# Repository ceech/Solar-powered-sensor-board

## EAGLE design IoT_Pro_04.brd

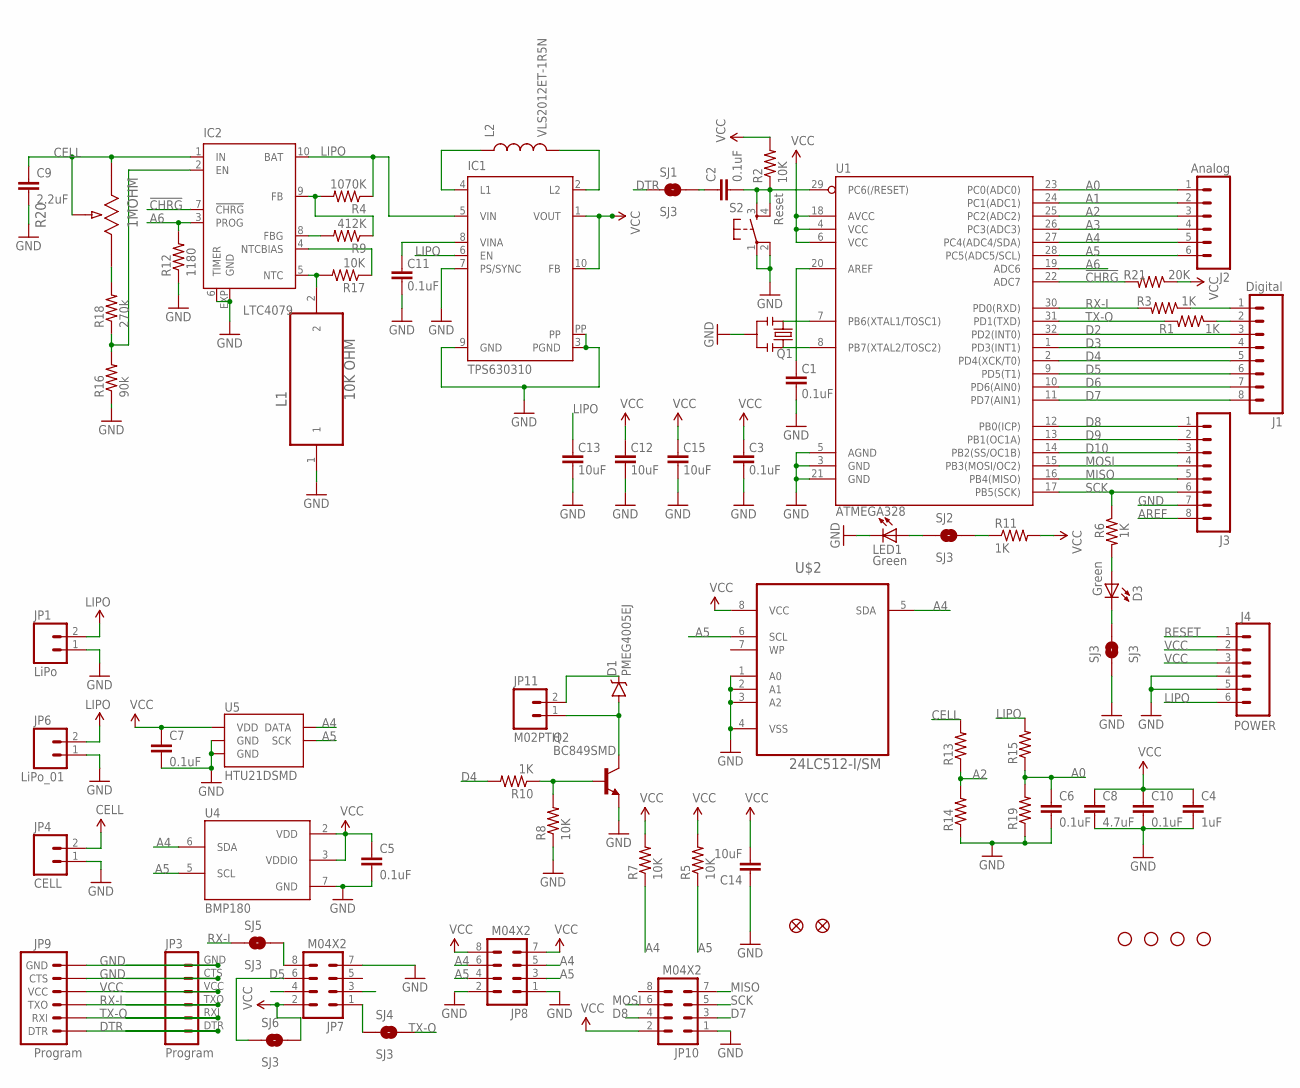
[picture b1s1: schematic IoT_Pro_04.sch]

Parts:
C1, C2, C3, C5, C6, C7, C10, C11: 0.1uF; 0805
C4: 1uF; 0805
C8: 4.7uF; 0805
C9: 2.2uF; 0805
C12, C13, C14, C15: 10uF; 0805
D1: PMEG4005EJ; SOD-323
D3: Green; PLCC2
IC1: TPS630310; S-PDSO-N10
IC2: LTC4079; DFN10-3X3
J1: Digital; 1X08
J2: Analog; 1X06
J3: M081X08; 1X08
J4: POWER; 1X06
JP1: LiPo; MOLEX-1X2
JP2, JP5: FIDUCIAL1X2.5; FIDUCIAL-1X2.5
JP3: Program; 1X06
JP4: CELL; MOLEX-1X2
JP6: LiPo_01; 1X02
JP7, JP8, JP10: M04X2; 2X4
JP9: Program; 1X06-SMD
JP11: M02PTH; 1X02
L1: 10K OHM; THERM_B57421V2103J62
L2: VLS2012ET-1R5N; 1007
LED1: Green; PLCC2
Q1: 8MHZ; RESONATOR-SMD
Q2: BC849SMD; SOT23-BEC
R1, R3, R6, R10, R11: 1K; 0805
R2, R5, R7, R8, R17: 10K; 0805
R4: 1070K; 0805
R9: 412K; 0805
R12: 1180; 0805
R13, R14, R15, R19: RESISTOR0805-RES; 0805
R16: 90k; 0805
R18: 270k; 0805
R20: 1MOHM; POT_EVM2N
R21: 20K; 0805
S2: Reset; TACTILE_SWITCH_SMD
SJ1, SJ2, SJ3, SJ4, SJ5, SJ6: SJ3; SJ_2S-NOTRACE
U1: ATMEGA328; TQFP32-08
U4: BMP180
U5: HTU21DSMD; HTU21D
U$1, U$3, U$9, U$10: STAND-OFFTIGHT; STAND-OFF-TIGHT
U$2: 24LC512-I/SM; SOIC127P794X203-8N

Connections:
!CHRG: IC2.7 (!CHRG), R21.2, U1.22 (ADC7)
A0: C6.1, J2.1, R15.1, R19.2, U1.23 (PC0(ADC0))
A1: J2.2, U1.24 (PC1(ADC1))
A2: J2.3, R13.1, R14.2, U1.25 (PC2(ADC2))
A3: J2.4, U1.26 (PC3(ADC3))
A4: J2.5, JP8.5, JP8.6, R7.1, U1.27 (PC4(ADC4/SDA)), U4.6 (SDA), U5.DATA, U$2.5 (SDA)
A5: J2.6, JP8.3, JP8.4, R5.1, U1.28 (PC5(ADC5/SCL)), U4.5 (SCL), U5.SCK, U$2.6 (SCL)
A6: IC2.3 (PROG), R12.2, U1.19 (ADC6)
AREF: C1.2, J3.8, U1.20 (AREF)
CELL: C9.1, IC2.1 (IN), JP4.2, R13.2, R20.2, R20.3
D2: J1.3, U1.32 (PD2(INT0))
D3: J1.4, U1.1 (PD3(INT1))
D4: J1.5, R10.2, U1.2 (PD4(XCK/T0))
D5: J1.6, JP7.6, SJ6.1, U1.9 (PD5(T1))
D6: J1.7, U1.10 (PD6(AIN0))
D7: J1.8, JP10.3, U1.11 (PD7(AIN1))
D8: J3.1, JP10.4, U1.12 (PB0(ICP))
D9: J3.2, U1.13 (PB1(OC1A))
D10: J3.3, U1.14 (PB2(SS/OC1B))
DTR: JP3.DTR (1), JP9.1 (DTR), SJ1.1
GND: C1.1, C3.1, C4.2, C5.2, C6.2, C7.2, C8.2, C9.2, C10.2, C11.1, C12.1, C13.1, C14.1, C15.1, IC1.3 (PGND), IC1.7 (PS/SYNC), IC1.9 (GND), IC1.PP, IC2.6 (TIMER), IC2.EXP (GND), J3.7, J4.4, J4.5, JP1.1, JP3.CTS (5), JP3.GND (6), JP4.1, JP6.1, JP7.7, JP8.1, JP8.2, JP9.5 (CTS), JP9.6 (GND), JP10.1, L1.1, LED1.C, Q1.2, Q2.E, R8.1, R12.1, R14.1, R16.1, R19.1, S2.1, S2.2, SJ3.1, U1.3 (GND), U1.5 (AGND), U1.21 (GND), U4.7 (GND), U5.7 (GND), U5.GND, U$2.1 (A0), U$2.2 (A1), U$2.3 (A2), U$2.4 (VSS)
LIPO: C13.2, IC1.5 (VIN), IC1.6 (EN), IC2.10 (BAT), J4.6, JP1.2, JP6.2, R4.1, R15.2
MISO: J3.5, JP10.7, U1.16 (PB4(MISO))
MOSI: J3.4, JP10.6, U1.15 (PB3(MOSI/OC2))
N: IC2.2 (EN), R16.2, R18.1
unnamed: C2.1, SJ1.2
unnamed: Q1.1, U1.8 (PB7(XTAL2/TOSC2))
unnamed: Q1.3, U1.7 (PB6(XTAL1/TOSC1))
unnamed: LED1.A, SJ2.1
unnamed: D3.A, R6.2
unnamed: R11.1, SJ2.2
unnamed: D3.C, SJ3.2
unnamed: IC2.9 (FB), R4.2, R9.1
unnamed: D1.A, JP11.1, Q2.C
unnamed: D1.C, JP11.2
unnamed: Q2.B, R8.2, R10.1
unnamed: R18.2, R20.1
unnamed: JP7.1, SJ4.1
unnamed: JP7.8, SJ5.2
unnamed: IC1.4 (L1), L2.1
unnamed: IC2.8 (FBG), R9.2
unnamed: IC2.4 (NTCBIAS), R17.1
unnamed: IC2.5 (NTC), L1.2, R17.2
unnamed: IC1.2 (L2), L2.2
unnamed: C11.2, IC1.8 (VINA)
RESET: C2.2, J4.1, R2.1, S2.3, S2.4, U1.29 (PC6(/RESET))
RX-I: JP3.TXO (3), JP9.3 (TXO), R3.2, SJ5.1, U1.30 (PD0(RXD))
RX-IP: J1.2, R1.1
SCK: J3.6, JP10.5, R6.1, U1.17 (PB5(SCK))
TX-O: JP3.RXI (2), JP9.2 (RXI), R1.2, SJ4.2, U1.31 (PD1(TXD))
TX-OP: J1.1, R3.1
VCC: C3.2, C4.1, C5.1, C7.1, C8.1, C10.1, C12.2, C14.2, C15.2, IC1.1 (VOUT), IC1.10 (FB), J4.2, J4.3, JP3.VCC (4), JP7.2, JP8.7, JP8.8, JP9.4 (VCC), JP10.2, R2.2, R5.2, R7.2, R11.2, R21.1, SJ6.2, U1.4 (VCC), U1.6 (VCC), U1.18 (AVCC), U4.2 (VDD), U4.3 (VDDIO), U5.VDD, U$2.8 (VCC)

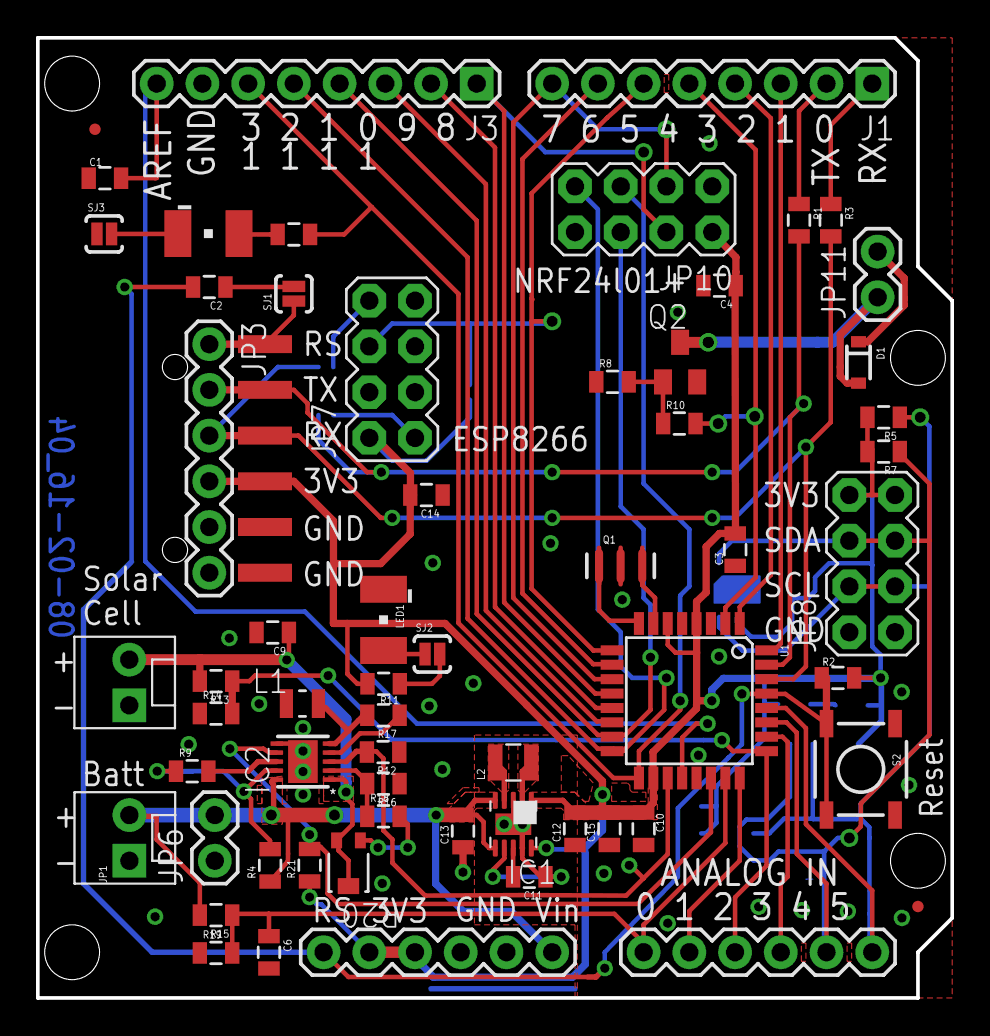
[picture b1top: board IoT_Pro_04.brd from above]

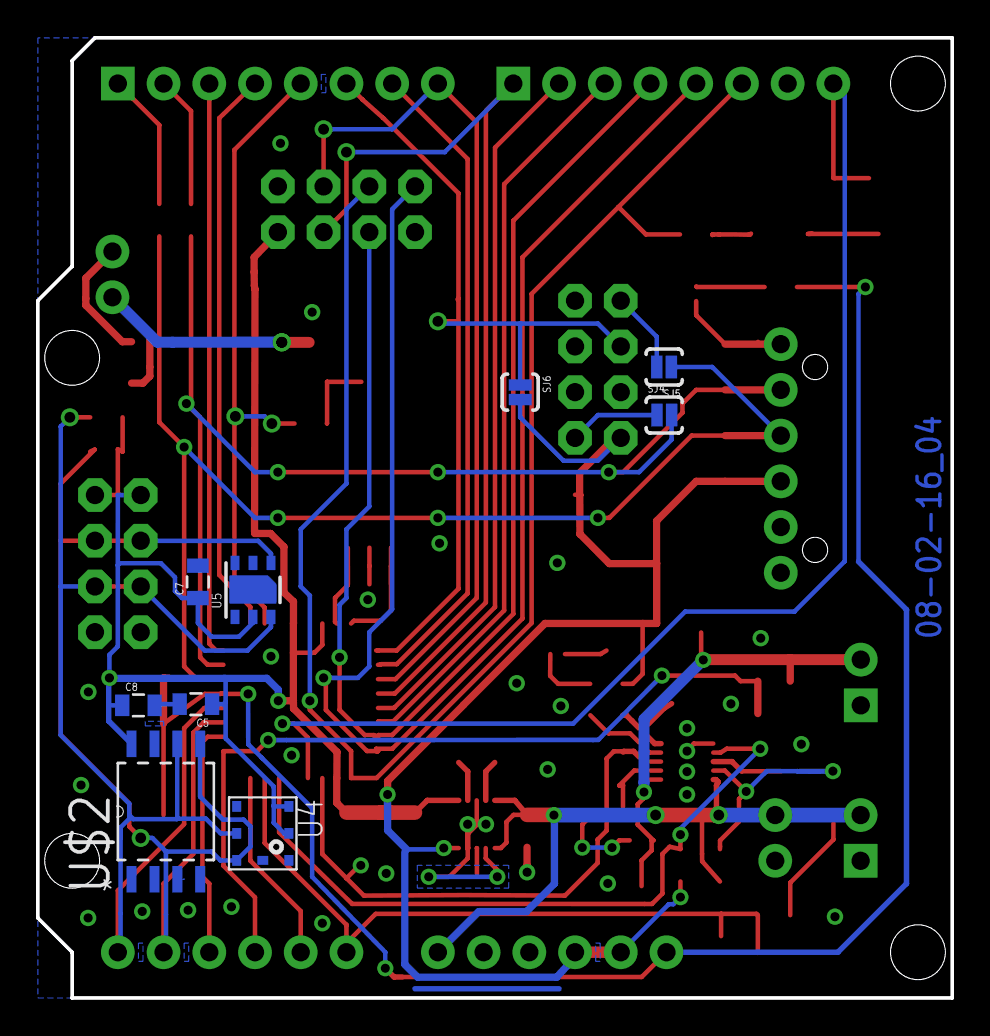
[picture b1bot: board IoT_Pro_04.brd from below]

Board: 2 copper layers, 50.8 x 53.3 mm, 75 parts (9 on the bottom side), 52 nets.

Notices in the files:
parts and their libraries:
SparkFun-Connectors: Licensing: Creative Commons ShareAlike 4.0 International - https://creativecommons.org/licenses/by-sa/4.0
